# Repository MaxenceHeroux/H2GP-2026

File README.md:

View this project on [CADLAB.io](https://cadlab.io/project/30325). 

# H2GP-2026

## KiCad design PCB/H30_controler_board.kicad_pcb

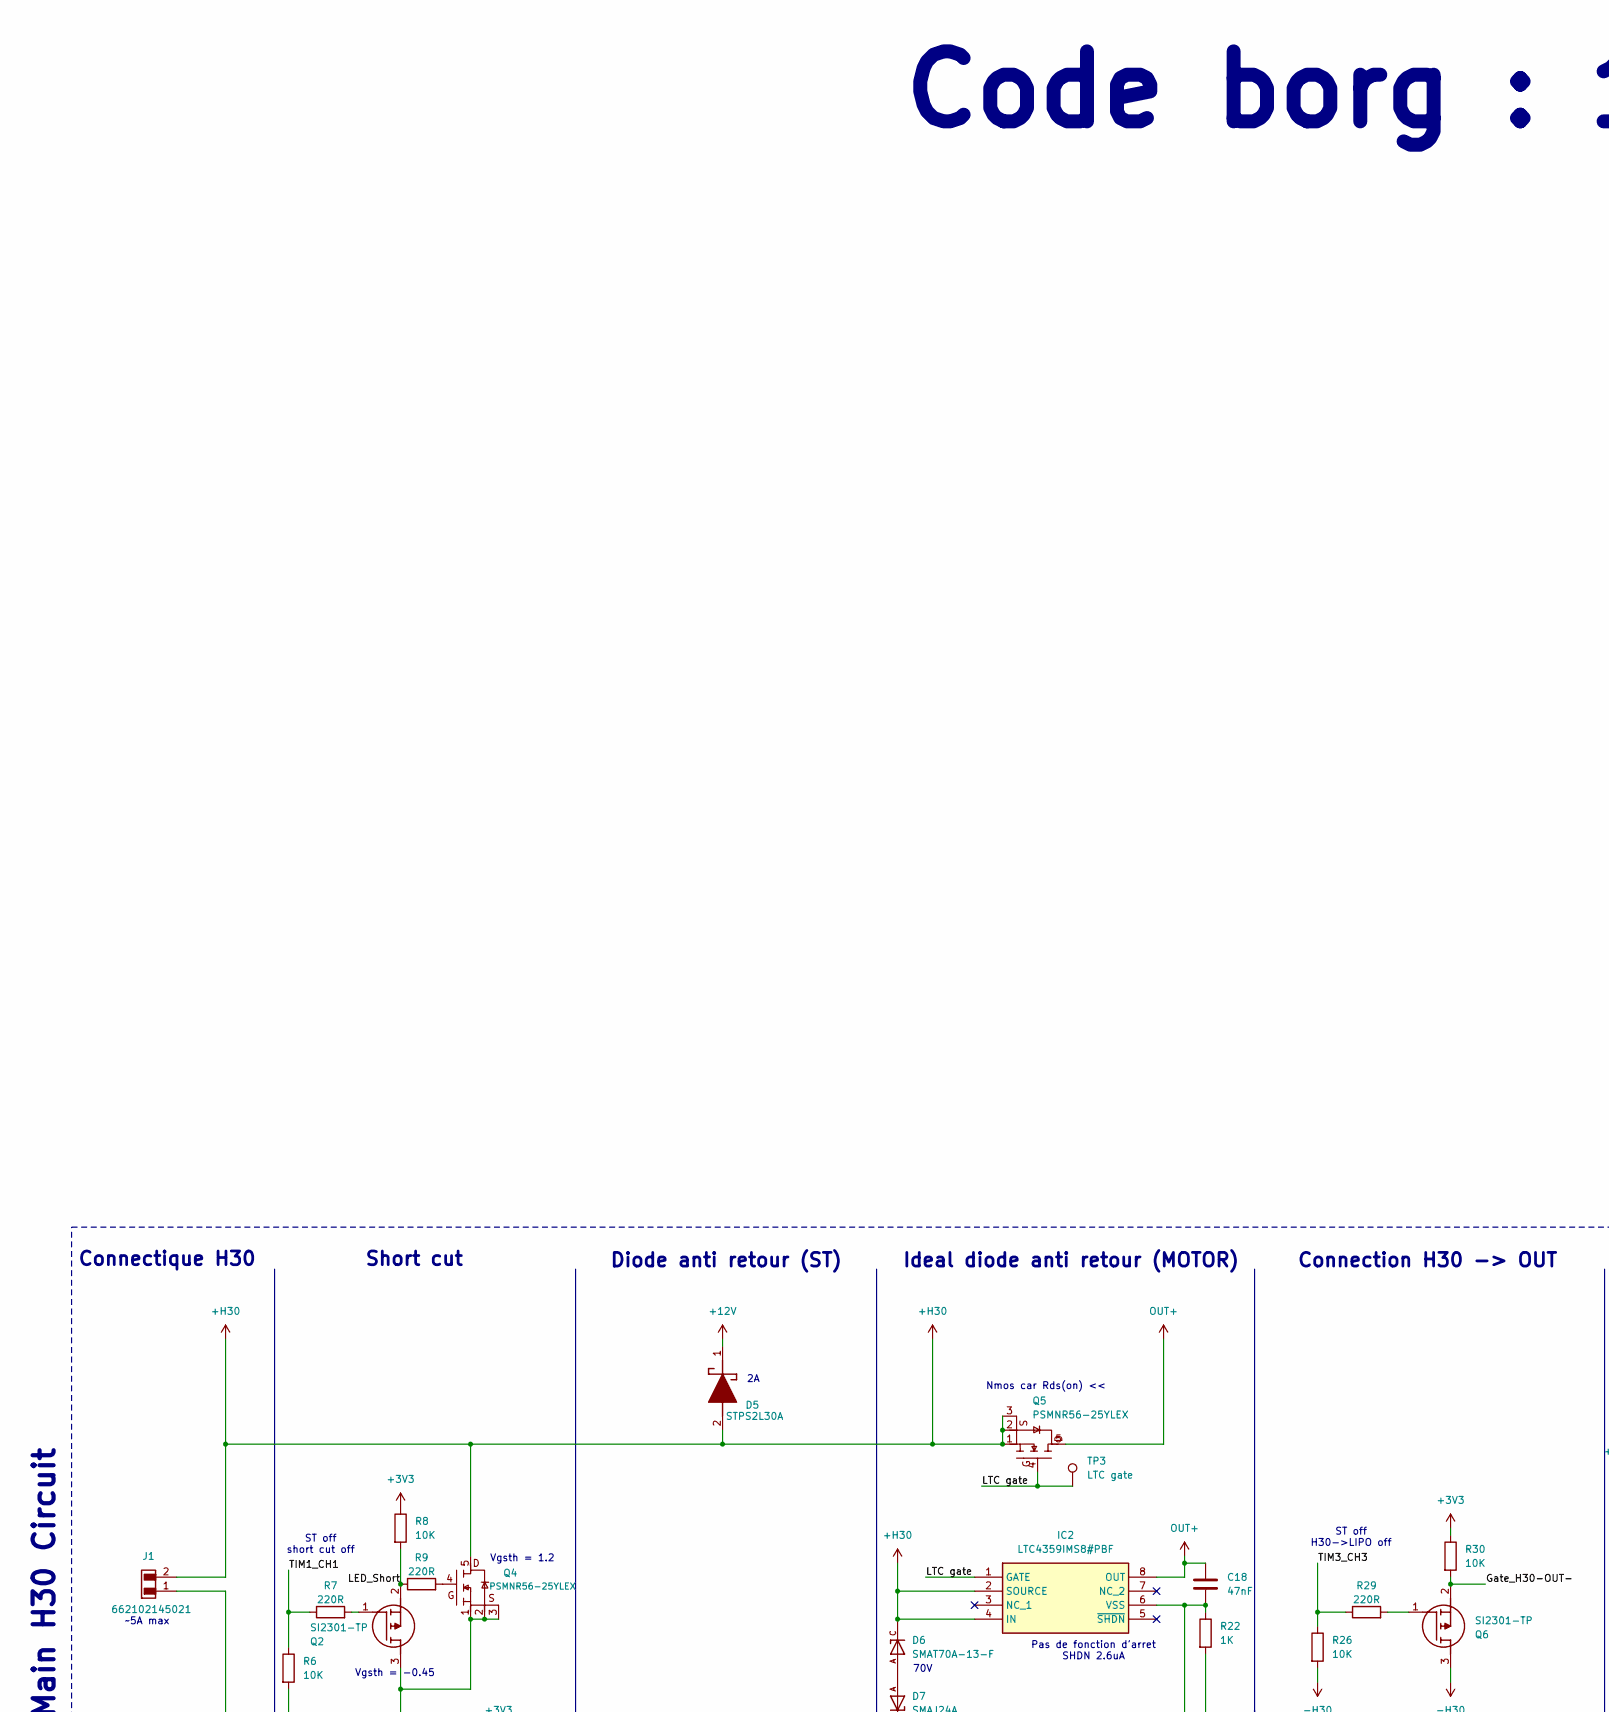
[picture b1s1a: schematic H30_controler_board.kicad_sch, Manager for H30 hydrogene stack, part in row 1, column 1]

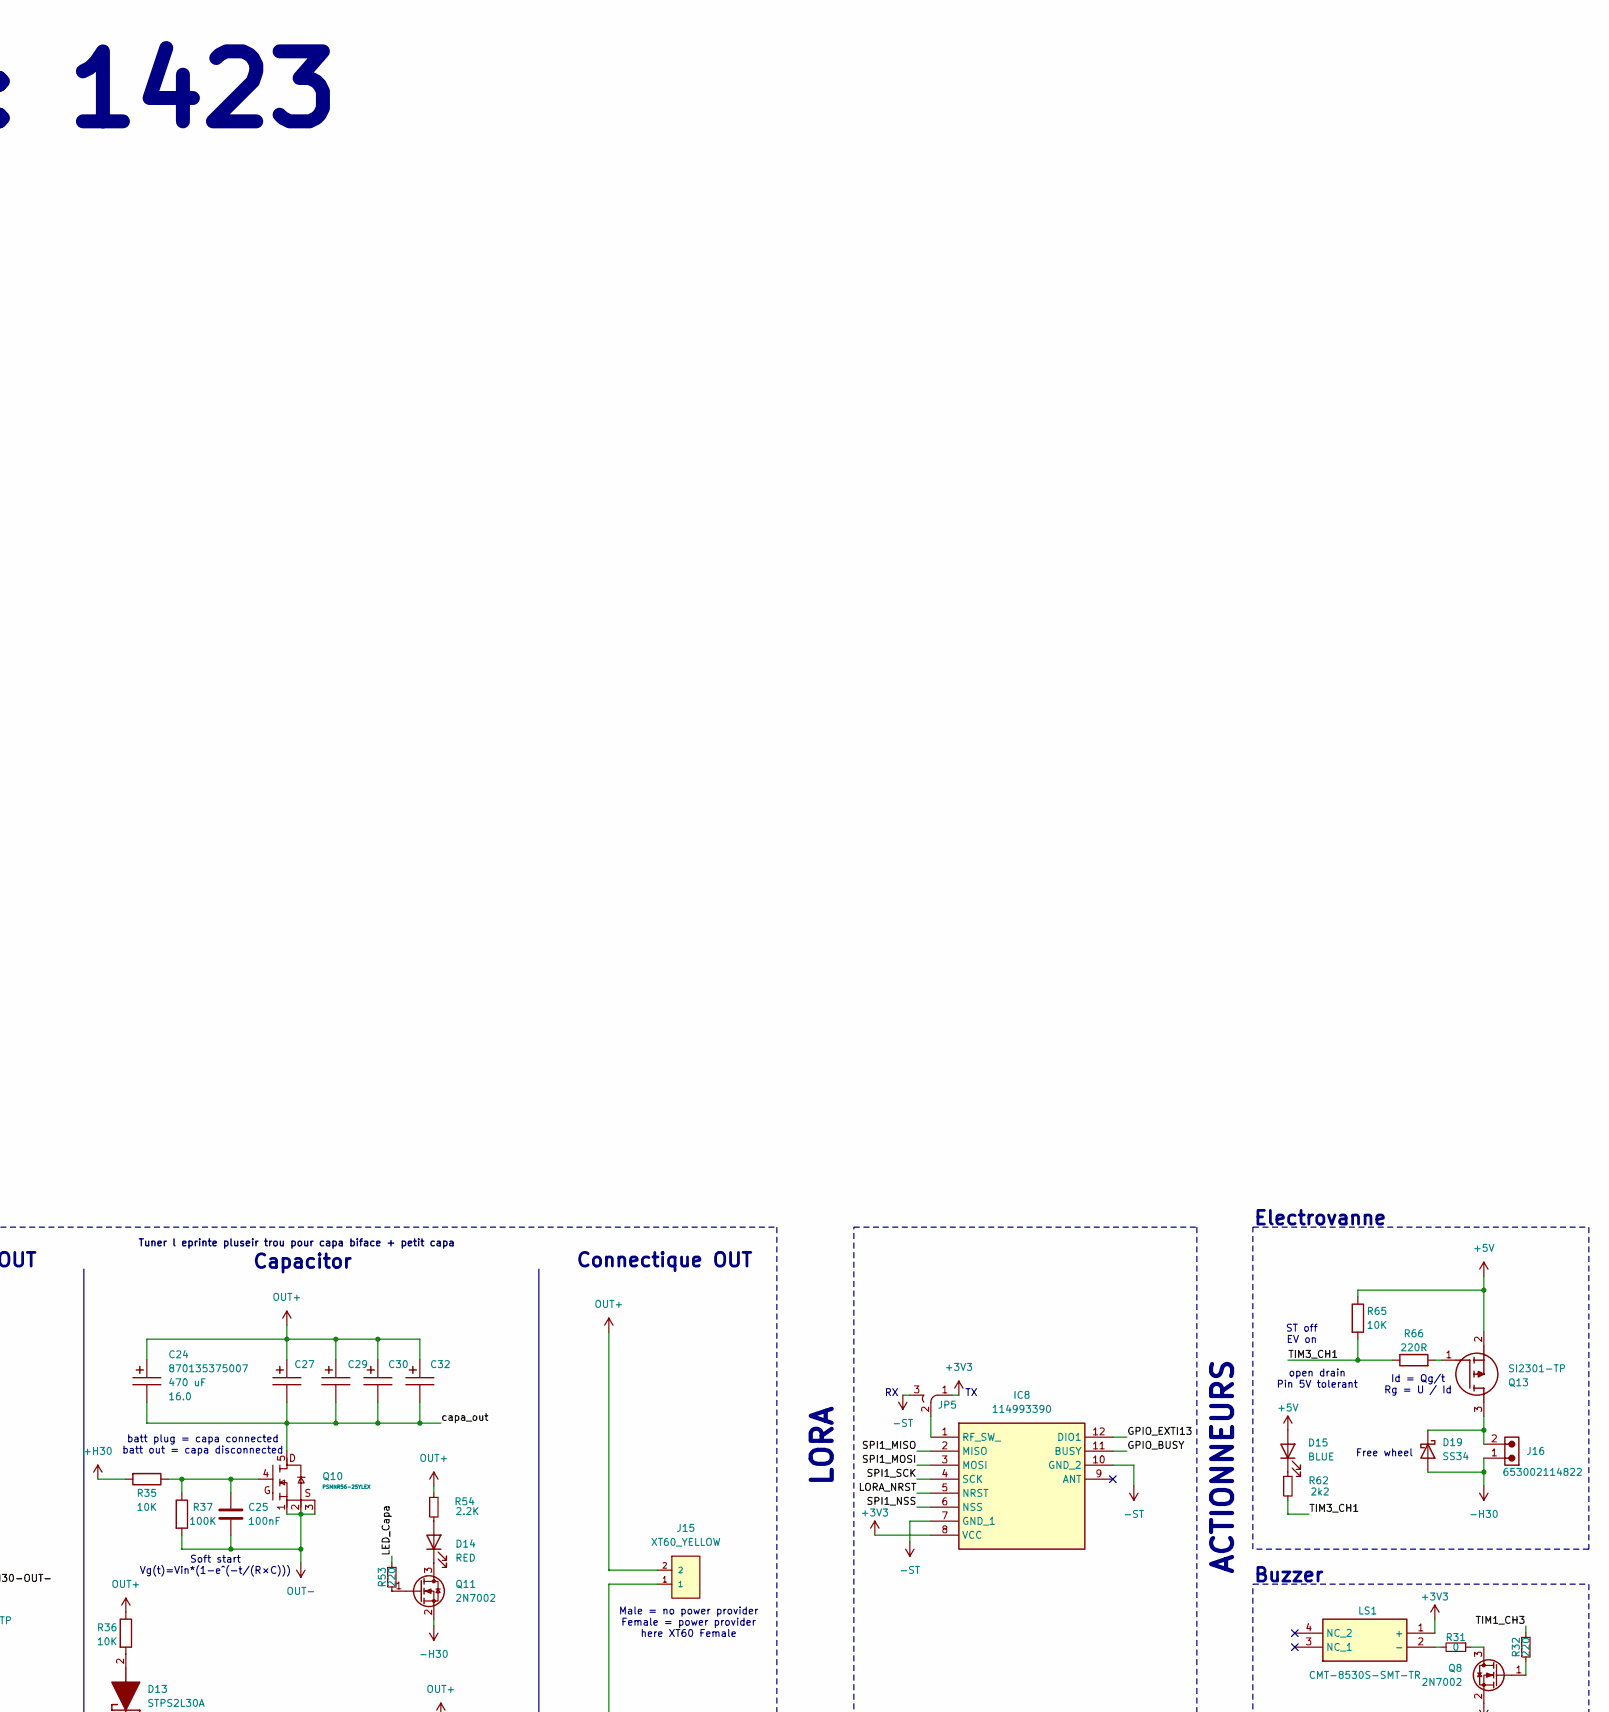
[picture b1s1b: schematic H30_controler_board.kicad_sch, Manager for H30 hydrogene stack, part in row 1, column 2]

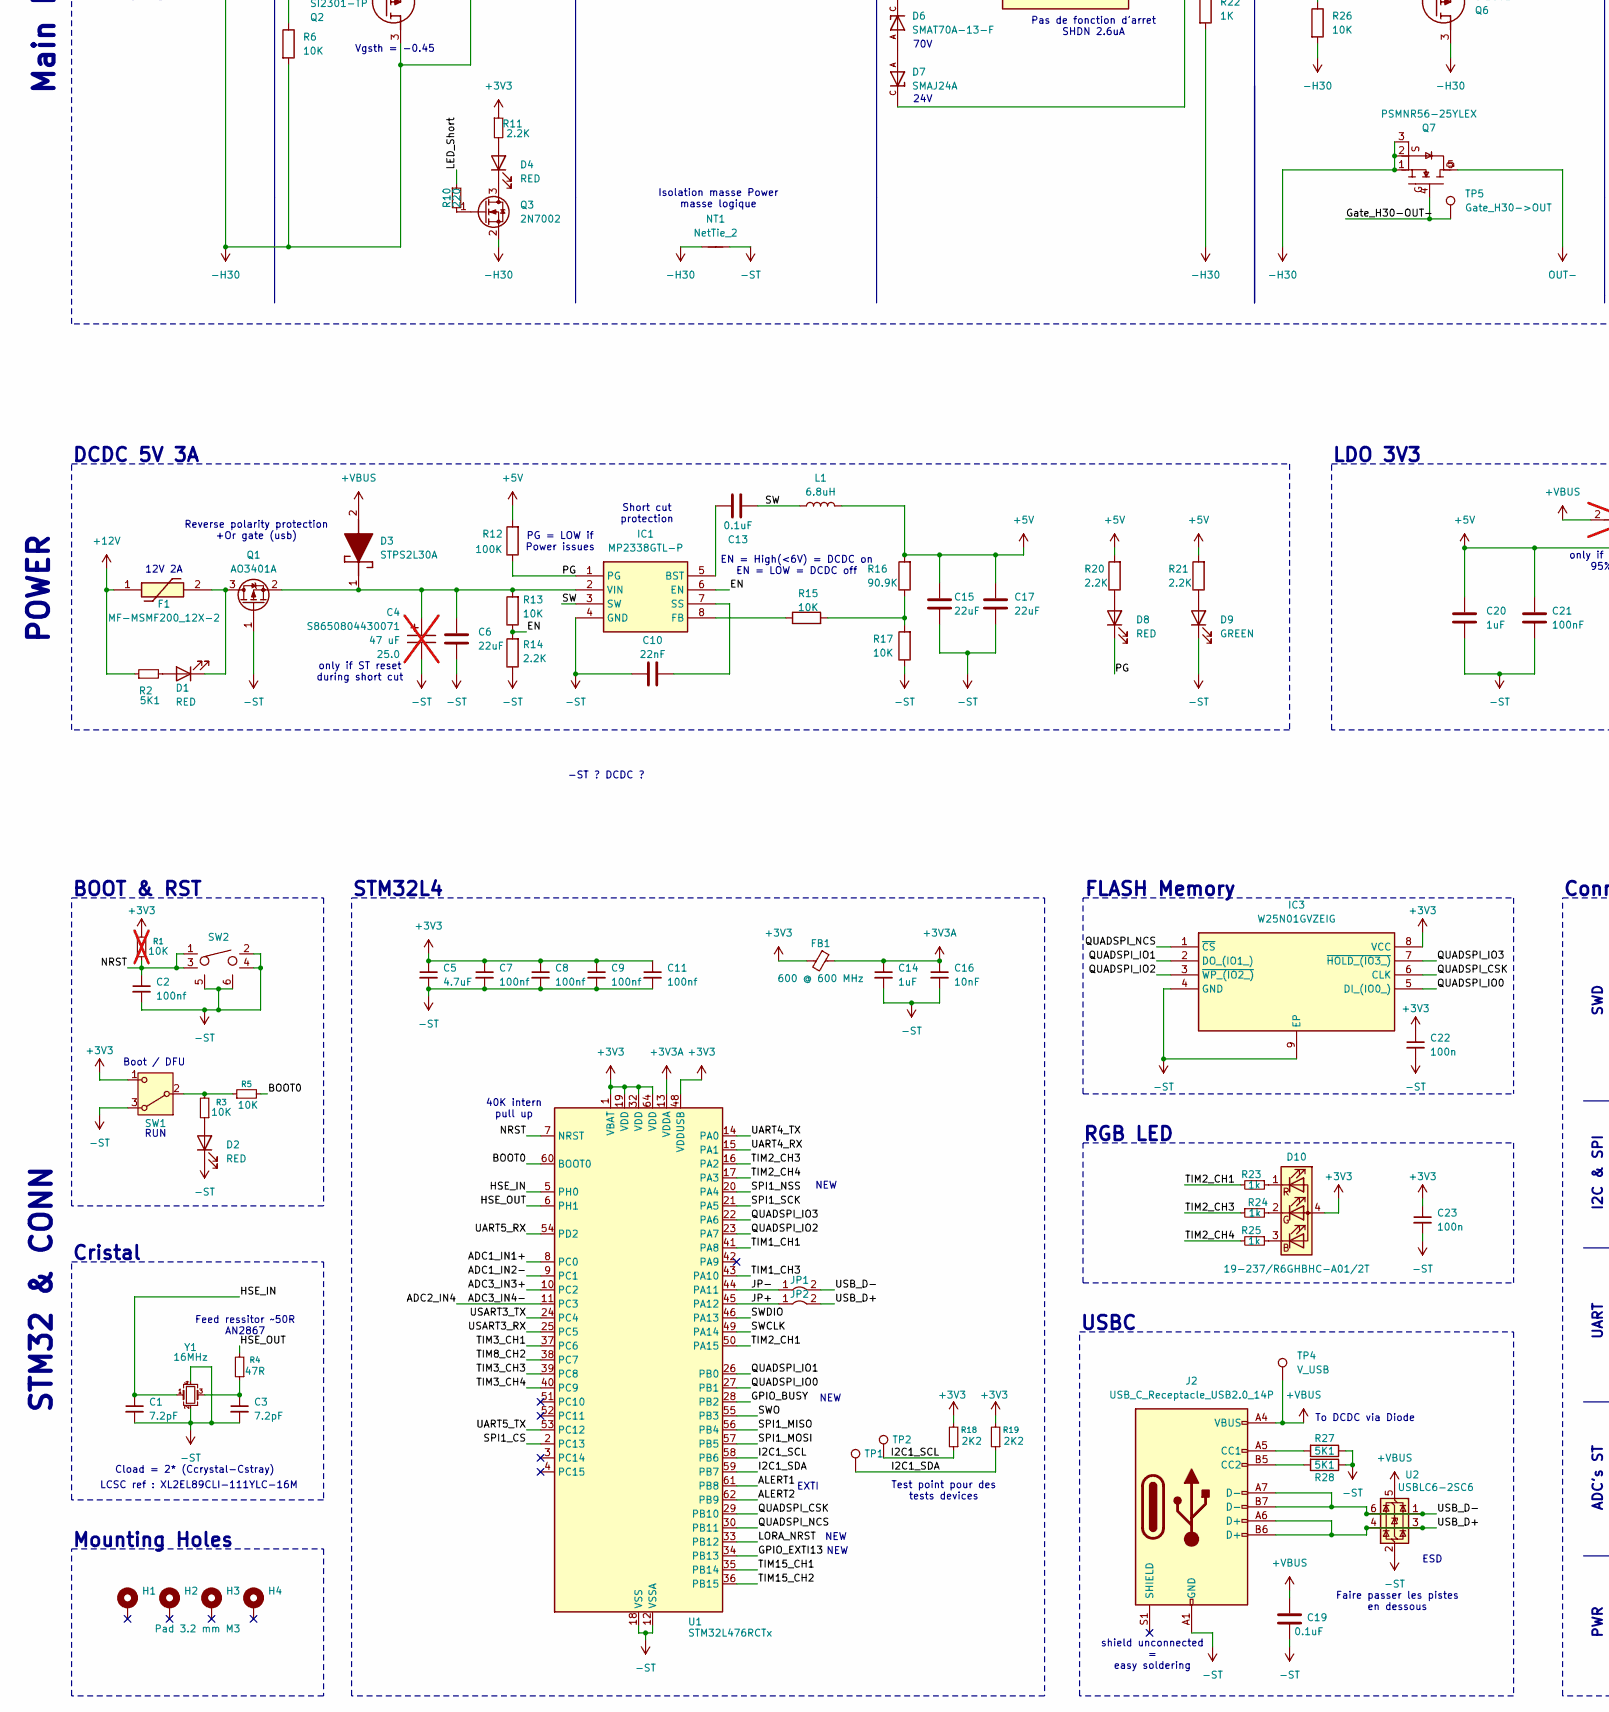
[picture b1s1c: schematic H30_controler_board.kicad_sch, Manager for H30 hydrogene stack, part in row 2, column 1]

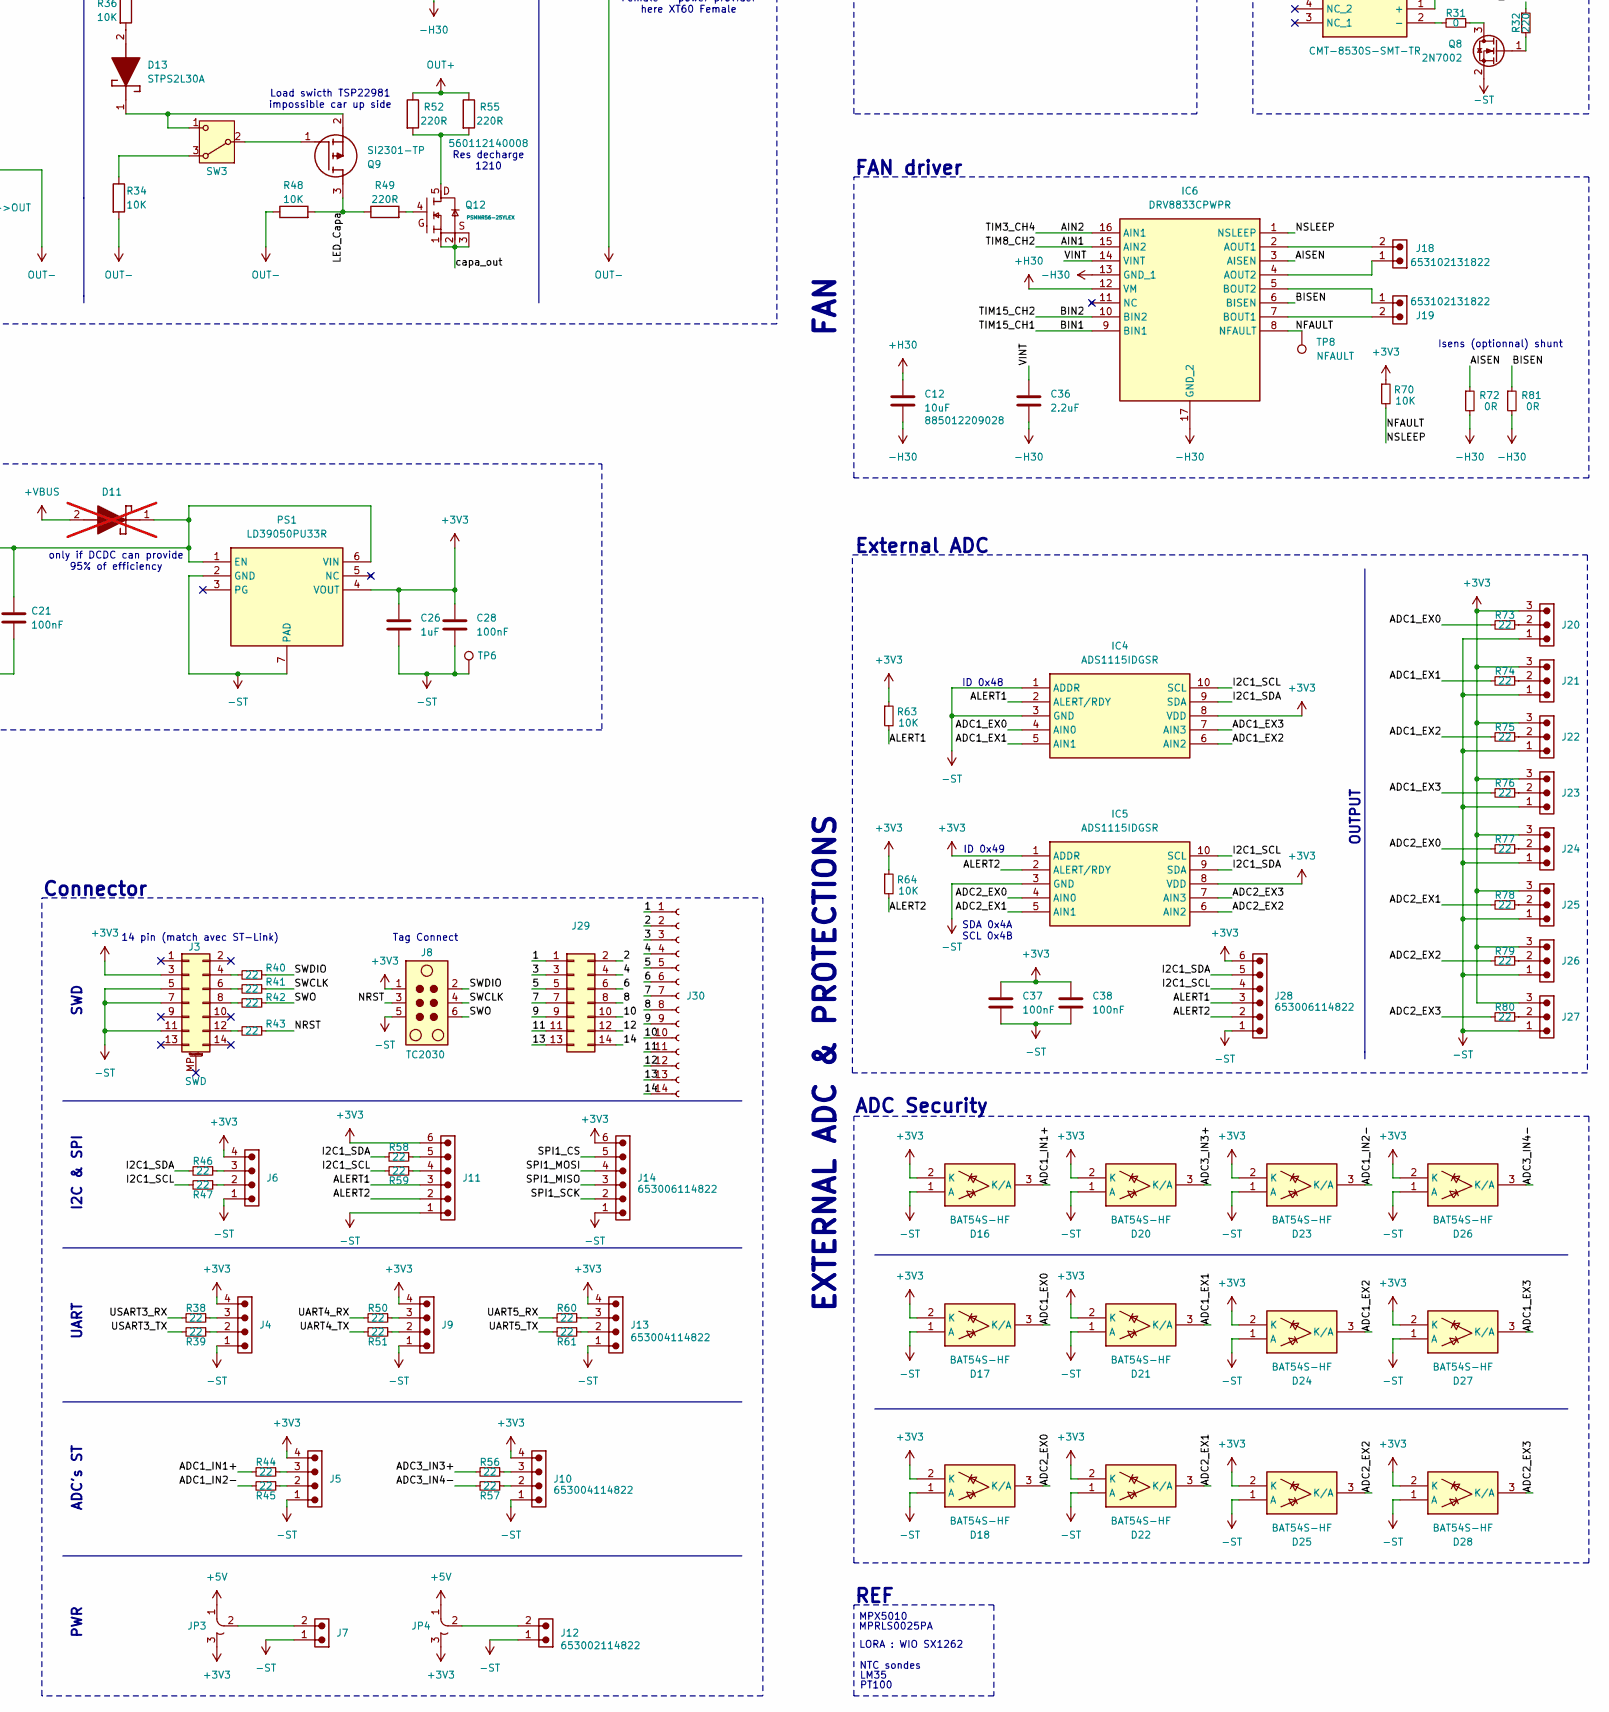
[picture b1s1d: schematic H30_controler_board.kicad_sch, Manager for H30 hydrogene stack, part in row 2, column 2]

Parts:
C1, C3: 7.2pF; C_0603_1608Metric
C2, C7, C9, C11: 100nf; C_0603_1608Metric
C4: 47 uF; CP_Wurth_WCAP-ASLI-D6.3L5.5; Voltage 25.0; Part Number S8650804430071; not fitted
C5: 4.7uF; C_0603_1608Metric
C6, C15, C17: 22uF; C_0603_1608Metric
C8: 100nf; C_0402_1005Metric
C10: 22nF; C_0603_1608Metric
C12: 10uF; C_1210_3225Metric
C13, C19: 0.1uF; C_0603_1608Metric
C14, C20, C26: 1uF; C_0603_1608Metric
C16: 10nF; C_0603_1608Metric
C18: 47nF; C_0603_1608Metric
C21, C25, C28, C37, C38: 100nF; C_0603_1608Metric
C22, C23: 100n; C_0603_1608Metric; LCSC Part # C1525
C24, C27, C29, C30, C32: 470 uF; CP_Wurth_WCAP-PTHT-P5D10L12.5; Voltage 16.0; Part Number 870135375007
C36: 2.2uF; C_0603_1608Metric
D1, D2, D4, D8, D14: RED; LED_0603_1608Metric
D3, D5, D13: STPS2L30A; DIOM5126X265N; Mouser Part Number 511-STPS2L30A
D6: SMAT70A-13-F; DIOM5226X230N; PARTREV 11 - 2
D7: SMAJ24A; DIOM4325X250N; PARTREV S2102
D9: GREEN; LED_0603_1608Metric
D10: 19-237/R6GHBHC-A01/2T; 19237R6GHBHCA012T; LCSC Part # C60105
D11: STPS2L30A; DIOM5126X265N; Mouser Part Number 511-STPS2L30A; not fitted
D15: BLUE; LED_0603_1608Metric
D16, D17, D18, D20, D21, D22, D23, D24, D25, D26, D27, D28: BAT54S-HF; SOT95P240X115-3N; Mouser Part Number 750-BAT54S-HF
D19: SS34; D_SMA
F1: MF-MSMF200_12X-2; MFMSMF20012X2; Manufacturer_Part_Number MF-MSMF200/12X-2
FB1: 600 @ 600 MHz; L_0805_2012Metric; LCSC Part # C1017
H1, H2, H4: MountingHole_Pad; MountingHole_3.2mm_M3_Pad_Via
H3: Pad 3.2 mm M3; MountingHole_3.2mm_M3_Pad_Via
IC1: MP2338GTL-P; SOTFL50P160X60-8N; Mouser Part Number 946-MP2338GTL-P
IC2: LTC4359IMS8#PBF; SOP65P490X110-8N; Mouser Part Number 584-LTC4359IMS8#PBF
IC3: W25N01GVZEIG; SON127P800X600X80-9N-D; Mouser Part Number 454-W25N01GVZEIG
IC4, IC5: ADS1115IDGSR; SOP50P490X110-10N; Mouser Part Number 595-ADS1115IDGSR
IC6: DRV8833CPWPR; SOP65P640X120-17N; Mouser Part Number 595-DRV8833CPWPR
IC8: 114993390; Mouser Part Number 713-114993390
J1: 662102145021; J_Wurth_WR-MPC3_662102145021; Working Voltage (V (AC)) 250
J2: USB_C_Receptacle_USB2.0_14P; USBC
J3: SWD; PinHeader_2x07_P1.27mm_Vertical
J4, J5, J6, J9, J10, J13: 653004114822; J_Wurth_WR-WTB_653004114822; Working Voltage (V (AC)) 125
J7, J12, J16: 653002114822; J_Wurth_WR-WTB_653002114822; Working Voltage (V (AC)) 125
J8: TC2030; Tag-Connect_TC2030-IDC-NL_2x03_P1.27mm_Vertical
J11, J14, J28: 653006114822; J_Wurth_WR-WTB_653006114822; Working Voltage (V (AC)) 125
J15: XT60_YELLOW; AMASS_XT60PB-F; PARTREV 1.2
J18, J19: 653102131822; J_Wurth_WR-WTB_653102131822; Working Voltage (V (AC)) 125
J20, J21, J22, J23, J24, J25, J26, J27: 653003114822; J_Wurth_WR-WTB_653003114822; Working Voltage (V (AC)) 125
J29: Conn_02x07_Odd_Even; PinSocket_2x07_P1.27mm_Vertical
J30: Conn_01x14_Socket; PinSocket_2x07_P2.54mm_Vertical
JP1, JP2: Jumper_0603
JP3, JP4, JP5: Jumper_3points_0402
L1: 6.8uH; INDPM5752X200N
LS1: CMT-8530S-SMT-TR; CMT8530SSMTTR; Mouser Part Number 490-CMT-8530S-SMT-TR
NT1: NetTie_2; NetTie-2_SMD_Pad2.0mm
PS1: LD39050PU33R; SON95P300X300X100-7N-D; Mouser Part Number 511-LD39050PU33R
Q1: AO3401A; SOT-23
Q2, Q6, Q9, Q13: SI2301-TP; SOT95P237X125-3N; Mouser Part Number 833-SI2301-TP
Q3, Q8, Q11: 2N7002; SOT-23
Q4, Q5, Q7, Q10, Q12: PSMNR56-25YLEX; PSMNR5830YLHX
R1: 10K; R_0402_1005Metric; not fitted
R2: 5K1; R_0603_1608Metric; LCSC Part # C25092
R3, R5, R6, R8, R13, R15, R17, R26, R30, R34, R35, R36, R48, R65: 10K; R_0603_1608Metric
R4: 47R; R_0603_1608Metric
R7, R9, R29, R49, R66: 220R; R_0603_1608Metric
R10, R32, R53: 220; R_0603_1608Metric; LCSC Part # C25092
R11, R54: 2.2K; R_0603_1608Metric; LCSC Part # C25092
R12, R37: 100K; R_0603_1608Metric
R14, R20, R21: 2.2K; R_0603_1608Metric
R16: 90.9K; R_0603_1608Metric
R18, R19: 2K2; R_0603_1608Metric
R22: 1K; R_0603_1608Metric
R23, R24, R25: 1k; R_0603_1608Metric; LCSC Part # C11702
R27, R28: 5K1; R_0603_1608Metric
R31: 0; R_0603_1608Metric; LCSC Part # C25092
R38, R39, R40, R41, R42, R43, R44, R45, R46, R47, R50, R51, R56, R57, R58, R59, R60, R61, R73, R74, R75, R76, R77, R78, R79, R80: 22; R_0402_1005Metric; LCSC Part # C25092
R52, R55: 220R; R_1210_3225Metric
R62: 2k2; R_0603_1608Metric; LCSC Part # C25092
R63, R64, R70: 10K; R_0603_1608Metric; LCSC Part # C25092
R72, R81: 0R; R_0603_1608Metric; LCSC Part # C25092
SW1, SW3: SW_Nidec_CAS-120A1; 450404015514
SW2: SKSG
TP1: SDA; TestPoint_Pad_D1.5mm
TP2: SCL; TestPoint_Pad_D1.5mm
TP3: LTC gate; TestPoint_Pad_D1.5mm
TP4: V_USB; TestPoint_Pad_D1.5mm
TP5: Gate_H30->OUT; TestPoint_Pad_D1.5mm
TP6: V_Reverse; TestPoint_Pad_D1.5mm
TP8: NFAULT; TestPoint_Pad_D1.5mm
U1: STM32L476RCTx; LQFP-64_10x10mm_P0.5mm
U2: USBLC6-2SC6; SOT-23-6
Y1: 16MHz; NX3225SA16000000MHZB3

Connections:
+3V3: C5.1, C7.1, C8.1, C9.1, C11.1, C22.1, C23.1, C26.1, C28.1, C37.1, C38.1, D10.4 (A), D16.2 (K), D17.2 (K), D18.2 (K), D20.2 (K), D21.2 (K), D22.2 (K), D23.2 (K), D24.2 (K), D25.2 (K), D26.2 (K), D27.2 (K), D28.2 (K), FB1.2, IC3.8 (VCC), IC4.8 (VDD), IC5.1 (ADDR), IC5.8 (VDD), IC8.8 (VCC), J3.3, J4.4, J5.4, J6.4, J8.1, J9.4, J10.4, J11.6, J13.4, J14.6, J20.3, J21.3, J22.3, J23.3, J24.3, J25.3, J26.3, J27.3, J28.6, JP3.3, JP4.3, JP5.1, LS1.1 (+), PS1.4 (VOUT), R1.2, R8.1, R11.1, R18.2, R19.2, R30.1, R63.1, R64.1, R70.1, SW1.1 (C), U1.1 (VBAT), U1.19 (VDD), U1.32 (VDD), U1.48 (VDDUSB), U1.64 (VDD); also elsewhere on the board
+3V3A: C14.1, C16.1, FB1.1, U1.13 (VDDA)
+5V: C15.1, C17.1, C20.1, C21.1, D11.1 (K), D15.2 (A), JP3.1, JP4.1, L1.2, PS1.1 (EN), PS1.6 (VIN), Q13.2 (S), R12.2, R16.2, R20.2, R21.2, R65.1
+12V: D5.1 (K), F1.1, R2.1
+H30: C12.1, D5.2 (A), D6.C, IC2.2 (SOURCE), IC2.4 (IN), IC6.12 (VM), J1.2, Q4.5 (D), Q4.6, Q5.1 (S), Q5.2 (S), Q5.3 (S), R35.2
+VBUS: C19.1, D3.2 (A), D11.2 (A), J2.A4 (VBUS), J2.A9 (VBUS), J2.B4 (VBUS), J2.B9 (VBUS), TP4.1, U2.5 (VBUS)
-H30: C12.2, C36.2, D19.2 (A), IC6.13 (GND_1), IC6.17 (GND_2), J1.1, J16.1, J19.MP1, NT1.2, Q2.3 (D), Q3.2 (S), Q4.1 (S), Q4.2 (S), Q4.3 (S), Q6.3 (D), Q7.1 (S), Q7.2 (S), Q7.3 (S), Q11.2 (S), R6.2, R22.2, R26.2, R72.2, R81.2
-ST: C1.2, C2.2, C3.2, C4.2, C5.2, C6.2, C7.2, C8.2, C9.2, C10.2, C11.2, C14.2, C15.2, C16.2, C17.2, C19.2, C20.2, C21.2, C22.2, C23.2, C26.2, C28.2, C37.2, C38.2, D2.1 (K), D9.1 (K), D16.1 (A), D17.1 (A), D18.1 (A), D20.1 (A), D21.1 (A), D22.1 (A), D23.1 (A), D24.1 (A), D25.1 (A), D26.1 (A), D27.1 (A), D28.1 (A), IC1.4 (GND), IC3.4 (GND), IC3.9 (EP), IC4.1 (ADDR), IC4.3 (GND), IC5.3 (GND), IC8.7 (GND_1), IC8.10 (GND_2), J2.A1 (GND), J2.A12 (GND), J2.B1 (GND), J2.B12 (GND), J3.5, J3.7, J3.11, J4.1, J5.1, J6.1, J7.1, J8.5, J9.1, J10.1, J11.1, J12.1, J13.1, J14.1, J20.1, J21.1, J22.1, J23.1, J24.1, J25.1, J26.1, J27.1, J28.1, JP5.3, NT1.1, PS1.2 (GND), PS1.7 (PAD), Q1.1 (G), Q8.2 (S), R14.1, R17.1, R27.1, R28.1, SW1.3 (A), SW2.2, SW2.4, SW2.5, SW2.6, TP6.1, U1.12 (VSSA), U1.18 (VSS), U1.31 (VSS), U1.47 (VSS), U1.63 (VSS), U2.2 (GND), Y1.2, Y1.4
/1: J29.1, J30.1
/2: J29.2, J30.2
/3: J29.3, J30.3
/4: J29.4, J30.4
/5: J29.5, J30.5
/6: J29.6, J30.6
/7: J29.7, J30.7
/8: J29.8, J30.8
/9: J29.9, J30.9
/10: J29.10, J30.10
/11: J29.11, J30.11
/12: J29.12, J30.12
/13: J29.13, J30.13
/14: J29.14, J30.14
/ADC1_EX0: D17.3 (K/A), IC4.4 (AIN0), R73.2
/ADC1_EX1: D21.3 (K/A), IC4.5 (AIN1), R74.2
/ADC1_EX2: D24.3 (K/A), IC4.6 (AIN2), R75.2
/ADC1_EX3: D27.3 (K/A), IC4.7 (AIN3), R76.2
/ADC1_IN1+: D16.3 (K/A), R44.2, U1.8 (PC0)
/ADC1_IN2-: D23.3 (K/A), R45.2, U1.9 (PC1)
/ADC2_EX0: D18.3 (K/A), IC5.4 (AIN0), R77.2
/ADC2_EX1: D22.3 (K/A), IC5.5 (AIN1), R78.2
/ADC2_EX2: D25.3 (K/A), IC5.6 (AIN2), R79.2
/ADC2_EX3: D28.3 (K/A), IC5.7 (AIN3), R80.2
/ADC2_IN4: D26.3 (K/A), R57.2, U1.11 (PC3)
/ADC3_IN3+: D20.3 (K/A), R56.2, U1.10 (PC2)
/AIN1: IC6.15 (AIN2), U1.38 (PC7)
/AIN2: IC6.16 (AIN1), U1.40 (PC9)
/AISEN: IC6.3 (AISEN), R72.1
/ALERT1: IC4.2 (ALERT/RDY), J11.3, J28.3, R63.2, U1.61 (PB8)
/ALERT2: IC5.2 (ALERT/RDY), J11.2, J28.2, R64.2, U1.62 (PB9)
/BIN1: IC6.9 (BIN1), U1.35 (PB14)
/BIN2: IC6.10 (BIN2), U1.36 (PB15)
/BISEN: IC6.6 (BISEN), R81.1
/BOOT0: R5.2, U1.60 (BOOT0)
/EN: IC1.6 (EN), R13.1, R14.2
/GPIO_BUSY: IC8.11 (BUSY), U1.28 (PB2)
/GPIO_EXTI13: IC8.12 (DIO1), U1.34 (PB13)
/Gate_H30-OUT-: Q6.2 (S), Q7.4 (G), R30.2, TP5.1
/HSE_IN: C1.1, U1.5 (PH0), Y1.1
/HSE_OUT: R4.2, U1.6 (PH1)
/I2C1_SCL: IC4.10 (SCL), IC5.10 (SCL), J28.4, R18.1, R47.2, R59.2, TP2.1, U1.58 (PB6); also elsewhere on the board
/I2C1_SDA: IC4.9 (SDA), IC5.9 (SDA), J28.5, R19.1, R46.2, R58.2, TP1.1, U1.59 (PB7); also elsewhere on the board
/JP+: JP2.1, U1.45 (PA12)
/JP-: JP1.1, U1.44 (PA11)
/LED_Capa: Q9.3 (D), R48.2, R49.1, R53.1
/LED_Short: Q2.2 (S), R8.2, R9.1, R10.1
/LORA_NRST: IC8.5 (NRST), U1.33 (PB12)
/LTC gate: IC2.1 (GATE), Q5.4 (G), TP3.1
/NFAULT: IC6.1 (NSLEEP), IC6.8 (NFAULT), R70.2, TP8.1
/NRST: C2.1, J8.3, R1.1, R43.1, SW2.1, SW2.3, U1.7 (NRST)
/PG: D8.1 (K), IC1.1 (PG), R12.1
/QUADSPI_CSK: IC3.6 (CLK), U1.29 (PB10)
/QUADSPI_IO0: IC3.5 (DI_(IO0_)), U1.27 (PB1)
/QUADSPI_IO1: IC3.2 (DO_(IO1_)), U1.26 (PB0)
/QUADSPI_IO2: IC3.3 (~WP_(IO2_)), U1.23 (PA7)
/QUADSPI_IO3: IC3.7 (~HOLD_(IO3_)), U1.22 (PA6)
/QUADSPI_NCS: IC3.1 (~CS), U1.30 (PB11)
/SPI1_CS: J14.5, U1.2 (PC13)
/SPI1_MISO: IC8.2 (MISO), J14.3, U1.56 (PB4)
/SPI1_MOSI: IC8.3 (MOSI), J14.4, U1.57 (PB5)
/SPI1_NSS: IC8.6 (NSS), U1.20 (PA4)
/SPI1_SCK: IC8.4 (SCK), J14.2, U1.21 (PA5)
/SW: C13.2, IC1.3 (SW), L1.1
/SWCLK: J8.4, R41.1, U1.49 (PA14)
/SWDIO: J8.2, R40.1, U1.46 (PA13)
/SWO: J8.6, R42.1, U1.55 (PB3)
/TIM1_CH1: R6.1, R7.1, U1.41 (PA8)
/TIM1_CH3: R32.1, U1.43 (PA10)
/TIM2_CH1: R23.2, U1.50 (PA15)
/TIM2_CH3: R24.1, U1.16 (PA2)
/TIM2_CH4: R25.2, U1.17 (PA3)
/TIM3_CH1: R62.2, R65.2, R66.1, U1.37 (PC6)
/TIM3_CH3: R26.1, R29.1, U1.39 (PC8)
/UART4_RX: R50.2, U1.15 (PA1)
/UART4_TX: R51.2, U1.14 (PA0)
/UART5_RX: R60.2, U1.54 (PD2)
/UART5_TX: R61.2, U1.53 (PC12)
/USART3_RX: R38.2, U1.25 (PC5)
/USART3_TX: R39.2, U1.24 (PC4)
/USB_D+: J2.A6 (D+), J2.B6 (D+), JP2.2, U2.3 (I/O2), U2.4 (I/O2)
/USB_D-: J2.A7 (D-), J2.B7 (D-), JP1.2, U2.1 (I/O1), U2.6 (I/O1)
/VINT: C36.1, IC6.14 (VINT)
/capa_out: C24.2, C27.2, C29.2, C30.2, C32.2, Q10.5 (D), Q10.6, Q12.1 (S), Q12.2 (S), Q12.3 (S)
unnamed: C3.1, R4.1, Y1.3
unnamed: D1.2 (A), R2.2
unnamed: D1.1 (K), F1.2, Q1.3 (D)
unnamed: D2.2 (A), R3.1
unnamed: C4.1, C6.1, D3.1 (K), IC1.2 (VIN), Q1.2 (S), R13.2
unnamed: D4.2 (A), R11.2
unnamed: D4.1 (K), Q3.3 (D)
unnamed: D6.A, D7.A
unnamed: D8.2 (A), R20.1
unnamed: D9.2 (A), R21.1
unnamed: D10.3 (BK), R25.1
unnamed: D10.2 (GK), R24.2
unnamed: D10.1 (RK), R23.1
unnamed: D13.2 (A), R36.2
unnamed: D13.1 (K), Q9.2 (S), SW3.1 (C)
unnamed: D14.2 (A), R54.2
unnamed: D14.1 (K), Q11.3 (D)
unnamed: D15.1 (K), R62.1
unnamed: D19.1 (K), J16.2, Q13.3 (D)
unnamed: C13.1, IC1.5 (BST)
unnamed: IC1.8 (FB), R15.1
unnamed: C10.1, IC1.7 (SS)
unnamed: C18.2, D7.C, IC2.6 (VSS), R22.1
unnamed: IC6.2 (AOUT1), J18.2
unnamed: IC6.4 (AOUT2), J18.1
unnamed: IC6.7 (BOUT1), J19.2
unnamed: IC6.5 (BOUT2), J19.1
unnamed: IC8.1 (RF_SW_), JP5.2
unnamed: J2.A5 (CC1), R27.2
unnamed: J2.B5 (CC2), R28.2
unnamed: J3.4, R40.2
unnamed: J3.6, R41.2
unnamed: J3.8, R42.2
unnamed: J3.12, R43.2
unnamed: J4.2, R39.1
unnamed: J4.3, R38.1
unnamed: J5.2, R45.1
unnamed: J5.3, R44.1
unnamed: J6.2, R47.1
unnamed: J6.3, R46.1
unnamed: J7.2, JP3.2
unnamed: J9.2, R51.1
unnamed: J9.3, R50.1
unnamed: J10.2, R57.1
unnamed: J10.3, R56.1
unnamed: J11.4, R59.1
unnamed: J11.5, R58.1
unnamed: J12.2, JP4.2
unnamed: J13.2, R61.1
unnamed: J13.3, R60.1
unnamed: J20.2, R73.1
unnamed: J21.2, R74.1
unnamed: J22.2, R75.1
unnamed: J23.2, R76.1
unnamed: J24.2, R77.1
unnamed: J25.2, R78.1
unnamed: J26.2, R79.1
unnamed: J27.2, R80.1
unnamed: LS1.2 (-), R31.2
unnamed: Q2.1 (G), R7.2
unnamed: Q3.1 (G), R10.2
unnamed: Q4.4 (G), R9.2
unnamed: Q6.1 (G), R29.2
unnamed: Q8.3 (D), R31.1
unnamed: Q8.1 (G), R32.2
unnamed: Q9.1 (G), SW3.2 (B)
unnamed: C25.1, Q10.4 (G), R35.1, R37.1
unnamed: Q11.1 (G), R53.2
unnamed: Q12.5 (D), Q12.6, R52.2, R55.2
unnamed: Q12.4 (G), R49.2
unnamed: Q13.1 (G), R66.2
unnamed: R15.2, R16.1, R17.2
unnamed: R3.2, R5.1, SW1.2 (B)
unnamed: R34.1, SW3.3 (A)
OUT+: C18.1, C24.1, C27.1, C29.1, C30.1, C32.1, IC2.8 (OUT), J15.2, LS1.3 (NC_1), Q5.5 (D), Q5.6, R36.1, R52.1, R54.1, R55.1
OUT-: C25.2, J15.1, Q7.5 (D), Q7.6, Q10.1 (S), Q10.2 (S), Q10.3 (S), R34.2, R37.2, R48.1

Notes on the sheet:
Faire passer les pistes en dessous
OUTPUT
Nmos car Rds(on) <<
Boot / DFU
Isolation masse Power masse logique
Tag Connect
SWD
shield unconnected = easy soldering
ID 0x49
ID 0x48
To DCDC via Diode
ST off EV on
Code borg : 1423
EXTI
PWR
Electrovanne
Reverse polarity protection +Or gate (usb)
Connectique OUT
Short cut
Res decharge 1210
Main H30 Circuit
MPRLS0025PA
LORA
12V 2A
only if DCDC can provide 95% of efficiency
Mounting Holes
LM35
NEW
Cload = 2* (Ccrystal-Cstray)
Test point pour des tests devices
PT100
Load swicth TSP22981 impossible car up side
UART
DCDC 5V 3A
Short cut protection
Tuner l eprinte pluseir trou pour capa biface + petit capa
NTC sondes
External ADC
Diode anti retour (ST)
batt plug = capa connected batt out = capa disconnected

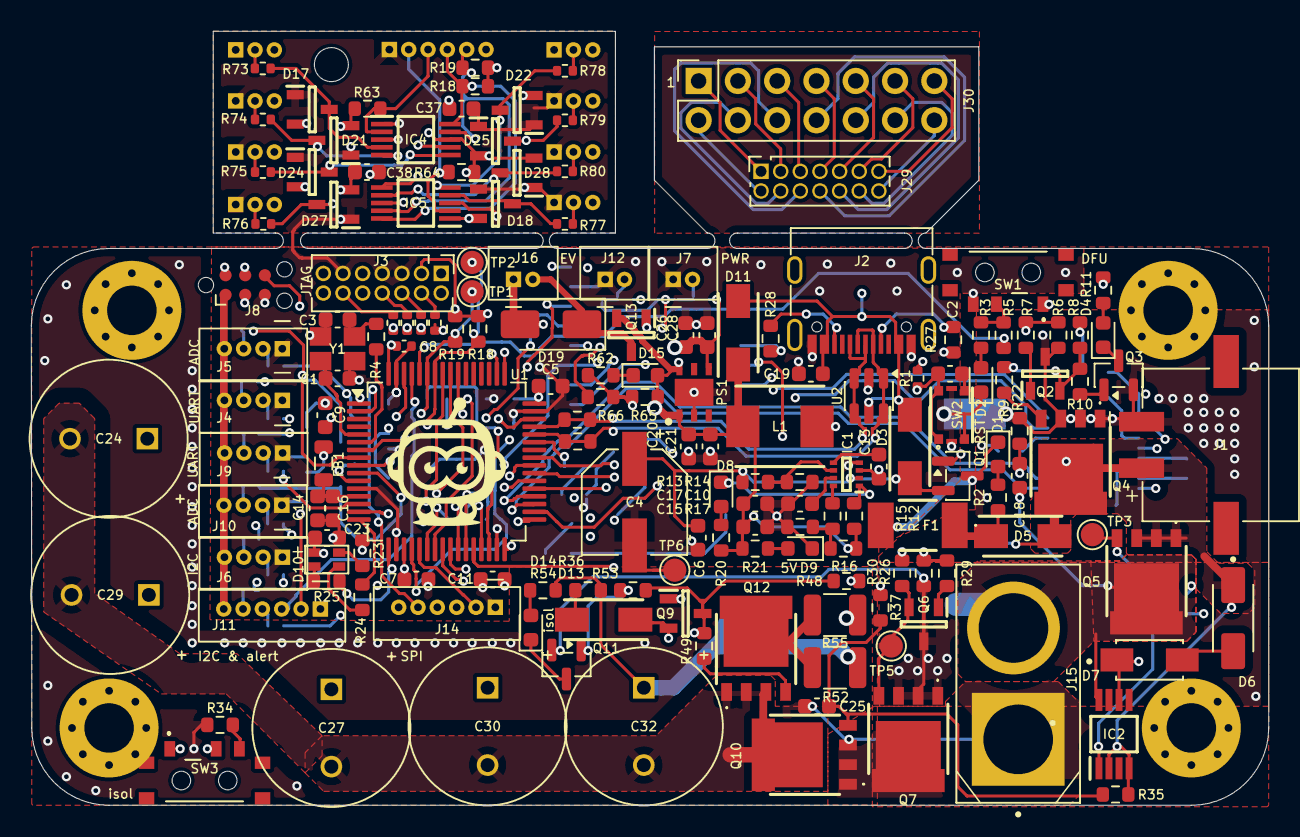
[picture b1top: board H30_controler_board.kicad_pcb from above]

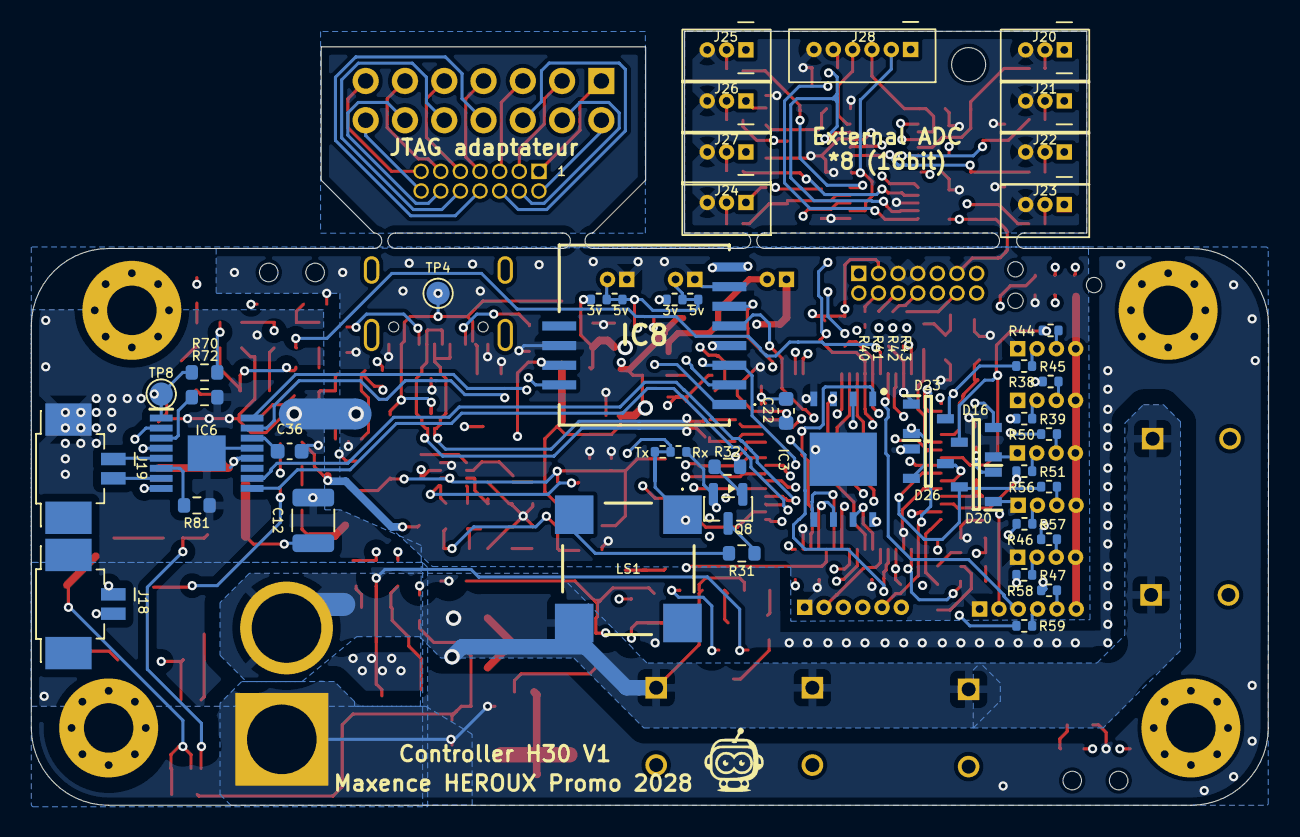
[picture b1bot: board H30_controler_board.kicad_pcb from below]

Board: 4 copper layers, 80.0 x 50.0 mm, 213 parts (46 on the bottom side), 164 nets.

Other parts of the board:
R18#2, R19#2: 2K2; R_0603_1608Metric

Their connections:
+3V3: R18#2.2, R19#2.2; also elsewhere on the board
/I2C1_SCL: R18#2.1; also elsewhere on the board
/I2C1_SDA: R19#2.1; also elsewhere on the board

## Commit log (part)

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2026-05-01 Add project title to README
2026-05-01 Backlink to CADLAB.io has been added.
2026-05-01 folder pcb
2026-05-01 add first layout
2026-05-06 upload V1
2026-05-21 V1.1
2026-05-22 PCB V1.1
2026-05-22 V1.2
2026-05-22 PCB V1.2
2026-06-12 ajout gitignore
2026-06-12 init projet stm32
2026-06-15 ajout fonctionnalités EV CC H30->ESC
2026-06-21 fan PWM + setup
2026-06-21 Code board / 5s
2026-06-23 LED RGB
2026-06-24 Temp + warning
2026-06-24 Tension sensor + Scan I2C
2026-06-25 LOG + PDMS
2026-06-25 Stream py
2026-06-28 lora + Regeneration + H2Trace
2026-06-30 lora qui marche nianiania
2026-06-30 lora lib
